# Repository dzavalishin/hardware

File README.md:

# hardware
Misc smart house hardware, kicad designs.

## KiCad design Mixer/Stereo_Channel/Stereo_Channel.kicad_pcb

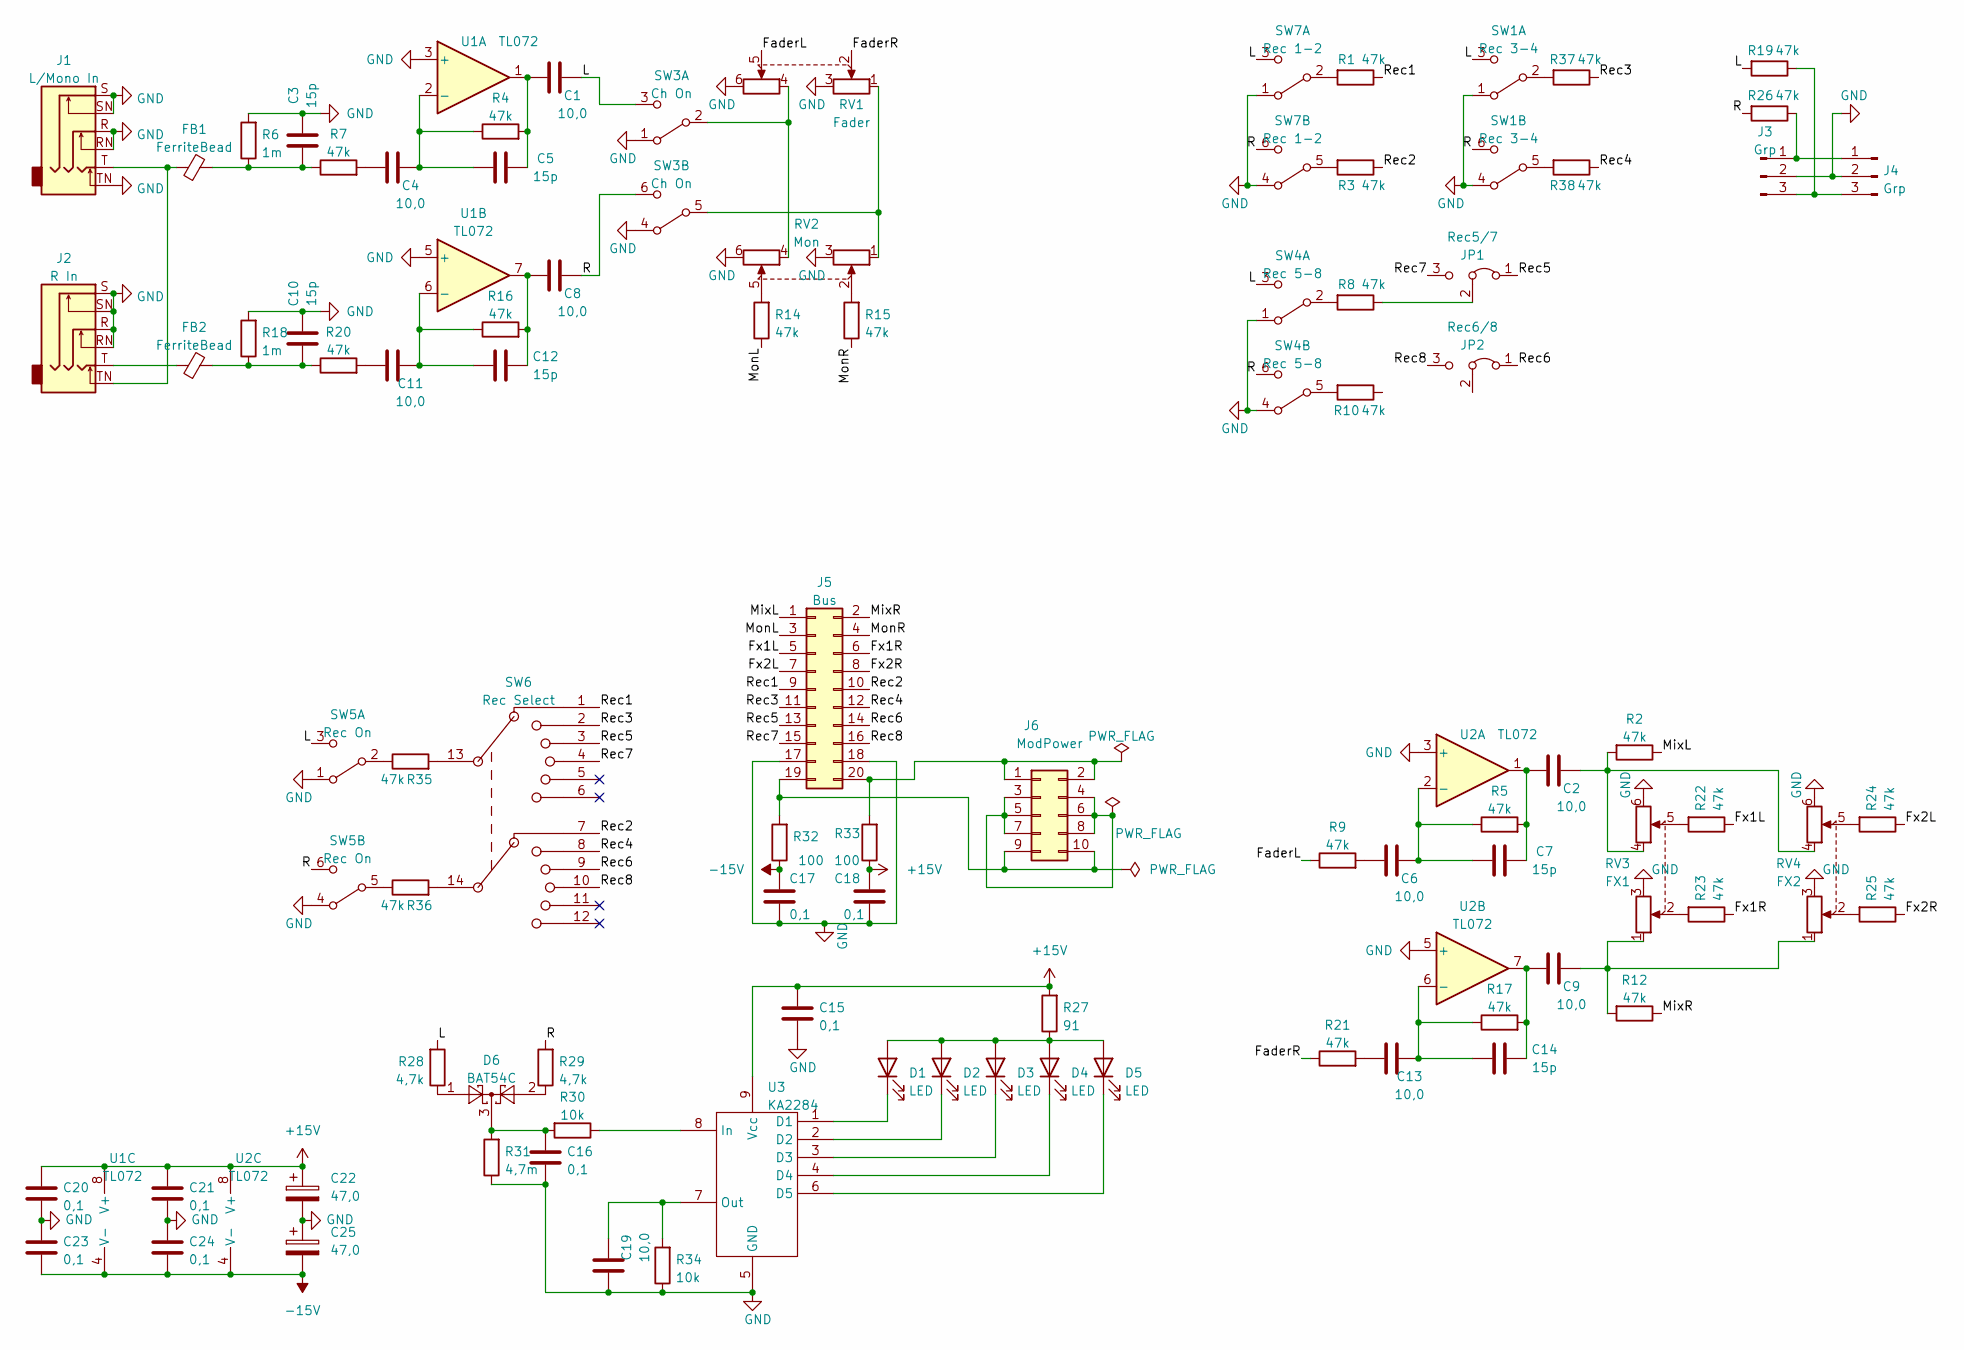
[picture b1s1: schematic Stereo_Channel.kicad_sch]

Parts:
C1, C2, C8, C9: 10,0; C_1206_3216Metric_Pad1.33x1.80mm_HandSolder
C3, C5, C7, C10, C12, C14: 15p; C_0805_2012Metric_Pad1.18x1.45mm_HandSolder
C4, C6, C11, C13, C19: 10,0; C_0805_2012Metric_Pad1.18x1.45mm_HandSolder
C15, C16, C17, C18, C20, C21, C23, C24: 0,1; C_1206_3216Metric_Pad1.33x1.80mm_HandSolder
C22, C25: 47,0; C_0805_2012Metric_Pad1.18x1.45mm_HandSolder
D1, D2, D3, D4, D5: LED; LED_Rectangular_W5.0mm_H2.0mm
D6: BAT54C; SOT-23
FB1, FB2: FerriteBead; L_Axial_L6.6mm_D2.7mm_P10.16mm_Horizontal_Vishay_IM-2
J1: L/Mono In; Jack_6.35mm_Neutrik_NMJ6HCD2_Horizontal
J2: R In; Jack_6.35mm_Neutrik_NMJ6HCD2_Horizontal
J3, J4: Grp; PinHeader_1x03_P2.54mm_Vertical
J5: Bus; PinHeader_2x10_P2.54mm_Vertical
J6: ModPower; PinHeader_2x05_P2.54mm_Vertical
JP1: Rec5/7; SolderJumper-3_P1.3mm_Bridged12_RoundedPad1.0x1.5mm_NumberL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
JP2: Rec6/8; SolderJumper-3_P1.3mm_Bridged12_RoundedPad1.0x1.5mm_NumberL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
R1, R2, R3, R4, R5, R7, R8, R9, R10, R12, R14, R15, R16, R17, R19, R20, R21, R22, R23, R24, R25, R26, R35, R36, R37, R38: 47k; R_1206_3216Metric_Pad1.30x1.75mm_HandSolder
R6, R18: 1m; R_1206_3216Metric_Pad1.30x1.75mm_HandSolder
R27: 91; R_1206_3216Metric_Pad1.30x1.75mm_HandSolder
R28, R29: 4,7k; R_1206_3216Metric_Pad1.30x1.75mm_HandSolder
R30, R34: 10k; R_1206_3216Metric_Pad1.30x1.75mm_HandSolder
R31: 4,7m; R_1206_3216Metric_Pad1.30x1.75mm_HandSolder
R32, R33: 100; R_1206_3216Metric_Pad1.30x1.75mm_HandSolder
RV1: Fader; Slider Pot 60mm
RV2: Mon; RK12 Duplex
RV3: FX1; RK12 Duplex
RV4: FX2; RK12 Duplex
SW1: Rec 3-4; Switch 2P2T 5.5x4.5mm Latched
SW3: Ch On; Switch 2P2T 5.5x4.5mm Latched
SW4: Rec 5-8; Switch 2P2T 5.5x4.5mm Latched
SW5: Rec On; Switch 2P2T 5.5x4.5mm Latched
SW6: Rec Select; SR16 Rotary Switch
SW7: Rec 1-2; Switch 2P2T 5.5x4.5mm Latched
U1, U2: TL072; DIP-8_W7.62mm_LongPads
U3: KA2284; SIP-9_22.3x3mm_P2.54mm

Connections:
+15V: C15.2, C18.2, C20.2, C21.2, C22.1, R27.2, R33.1, U1.8 (V+), U2.8 (V+), U3.9 (Vcc)
-15V: C17.2, C23.1, C24.1, C25.2, R32.1, U1.4 (V-), U2.4 (V-)
/FaderL: R9.1, RV1.5
/FaderR: R21.1, RV1.2
/Fx1L: J5.5, R22.1
/Fx1R: J5.6, R23.1
/Fx2L: J5.7, R24.1
/Fx2R: J5.8, R25.1
/L: C1.2, R19.2, R28.2, SW1.3 (C), SW3.3 (C), SW4.3 (C), SW5.3 (C), SW7.3 (C)
/MixL: J5.1, R2.1
/MixR: J5.2, R12.1
/MonL: J5.3, R14.1
/MonR: J5.4, R15.1
/R: C8.2, R26.2, R29.2, SW1.6 (C), SW3.6 (C), SW4.6 (C), SW5.6 (C), SW7.6 (C)
/Rec1: J5.9, R1.1, SW6.1
/Rec2: J5.10, R3.1, SW6.7
/Rec3: J5.11, R37.1, SW6.2
/Rec4: J5.12, R38.1, SW6.8
/Rec5: J5.13, JP1.1 (A), SW6.3
/Rec6: J5.14, JP2.1 (A), SW6.9
/Rec7: J5.15, JP1.3 (B), SW6.4
/Rec8: J5.16, JP2.3 (B), SW6.10
GND: C3.2, C10.2, C15.1, C16.1, C17.1, C18.1, C19.1, C20.1, C21.1, C22.2, C23.2, C24.2, C25.1, J1.R, J1.RN, J1.S, J1.SN, J1.TN, J2.R, J2.RN, J2.S, J2.SN, J3.2, J4.2, J5.17, J5.18, R6.2, R18.2, R31.1, R34.1, RV1.3, RV1.6, RV2.3, RV2.6, RV3.3, RV3.6, RV4.3, RV4.6, SW1.1 (A), SW1.4 (A), SW3.1 (A), SW3.4 (A), SW4.1 (A), SW4.4 (A), SW5.1 (A), SW5.4 (A), SW7.1 (A), SW7.4 (A), U1.3 (+), U1.5 (+), U2.3 (+), U2.5 (+), U3.5 (GND)
unnamed: C1.1, C5.2, R4.2, U1.1
unnamed: C2.1, C7.2, R5.2, U2.1
unnamed: C2.2, R2.2, RV3.4, RV4.4
unnamed: C3.1, FB1.2, R6.1, R7.1
unnamed: C4.1, R7.2
unnamed: C4.2, C5.1, R4.1, U1.2 (-)
unnamed: C6.1, R9.2
unnamed: C6.2, C7.1, R5.1, U2.2 (-)
unnamed: C9.2, R12.2, RV3.1, RV4.1
unnamed: C10.1, FB2.2, R18.1, R20.1
unnamed: C11.1, R20.2
unnamed: C11.2, C12.1, R16.1, U1.6 (-)
unnamed: C8.1, C12.2, R16.2, U1.7
unnamed: C13.1, R21.2
unnamed: C13.2, C14.1, R17.1, U2.6 (-)
unnamed: C9.1, C14.2, R17.2, U2.7
unnamed: C16.2, D6.3, R30.2, R31.2
unnamed: C19.2, R34.2, U3.7 (Out)
unnamed: D1.1 (K), U3.1 (D1)
unnamed: D1.2 (A), D2.2 (A), D3.2 (A), D4.2 (A), D5.2 (A), R27.1
unnamed: D2.1 (K), U3.2 (D2)
unnamed: D3.1 (K), U3.3 (D3)
unnamed: D4.1 (K), U3.4 (D4)
unnamed: D5.1 (K), U3.6 (D5)
unnamed: D6.1, R28.1
unnamed: D6.2, R29.1
unnamed: FB1.1, J1.T, J2.TN
unnamed: FB2.1, J2.T
unnamed: J3.1, J4.1, R26.1
unnamed: J3.3, J4.3, R19.1
unnamed: J5.19, J6.9, J6.10, R32.2
unnamed: J5.20, J6.1, J6.2, R33.2
unnamed: J6.3, J6.4, J6.5, J6.6, J6.7, J6.8
unnamed: JP1.2 (C), R8.1
unnamed: R1.2, SW7.2 (B)
unnamed: R3.2, SW7.5 (B)
unnamed: R8.2, SW4.2 (B)
unnamed: R10.2, SW4.5 (B)
unnamed: R14.2, RV2.5
unnamed: R15.2, RV2.2
unnamed: R22.2, RV3.5
unnamed: R23.2, RV3.2
unnamed: R24.2, RV4.5
unnamed: R25.2, RV4.2
unnamed: R30.1, U3.8 (In)
unnamed: R37.2, SW1.2 (B)
unnamed: R38.2, SW1.5 (B)
unnamed: RV1.1, RV2.1, SW3.5 (B)
unnamed: RV1.4, RV2.4, SW3.2 (B)
unnamed: R35.1, SW5.2 (B)
unnamed: R36.1, SW5.5 (B)
unnamed: R35.2, SW6.13
unnamed: R36.2, SW6.14

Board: 2 copper layers, 90 parts (66 on the bottom side), 76 nets, no tracks yet.

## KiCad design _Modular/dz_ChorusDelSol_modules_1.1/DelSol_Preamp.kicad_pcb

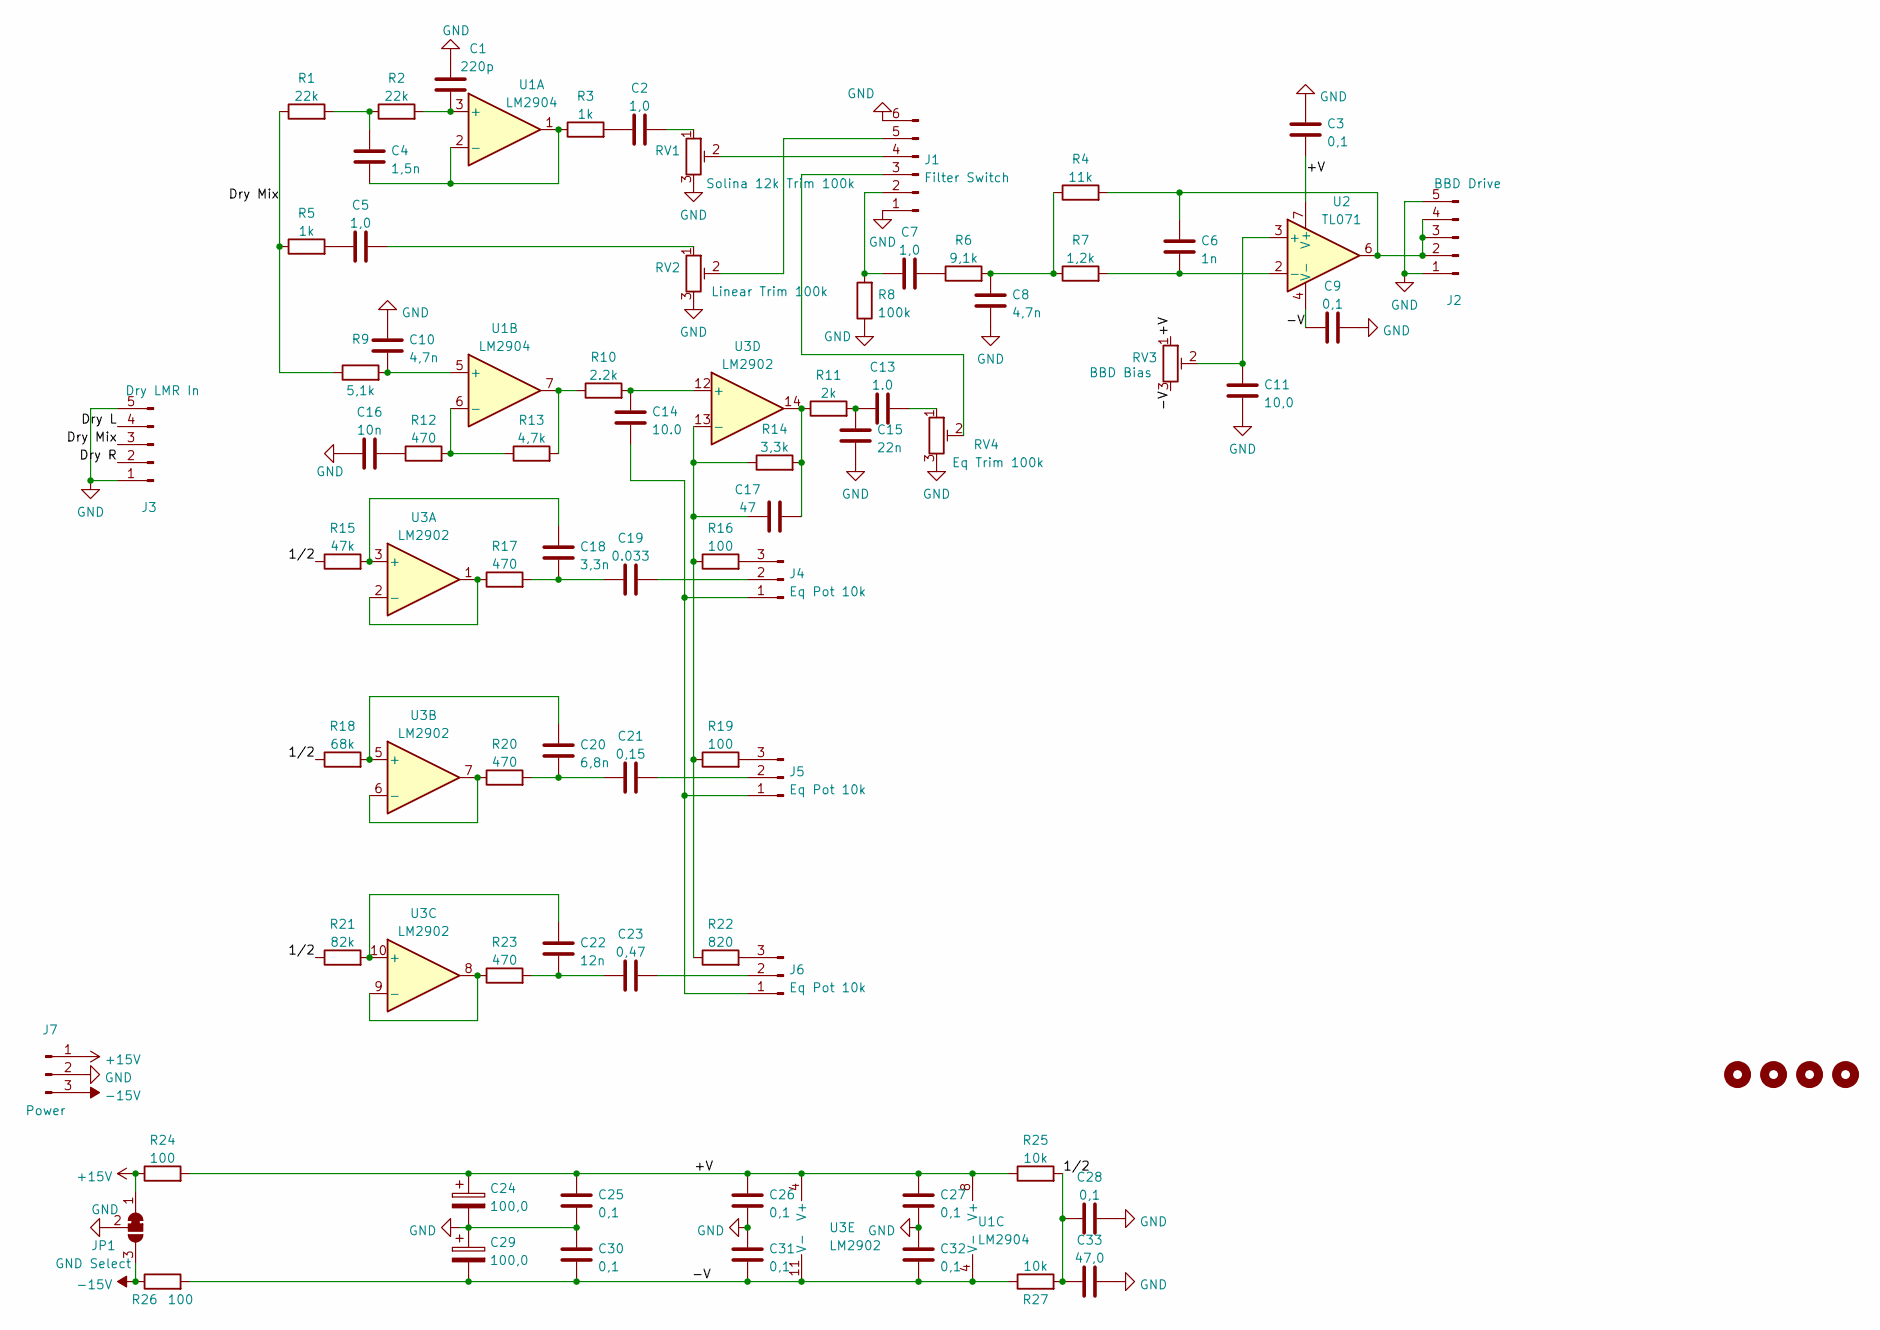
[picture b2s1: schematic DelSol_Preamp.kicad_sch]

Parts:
C1: 220p; C_Disc_D5.0mm_W2.5mm_P2.50mm
C2, C5, C7: 1,0; C_0805_2012Metric_Pad1.18x1.45mm_HandSolder
C3, C9, C25, C26, C27, C28, C30, C31, C32: 0,1; C_1206_3216Metric_Pad1.33x1.80mm_HandSolder
C4: 1,5n; C_Disc_D5.0mm_W2.5mm_P2.50mm
C6: 1n; C_0805_2012Metric_Pad1.18x1.45mm_HandSolder
C8, C10: 4,7n; C_0805_2012Metric_Pad1.18x1.45mm_HandSolder
C11: 10,0; C_0805_2012Metric_Pad1.18x1.45mm_HandSolder
C13: 1.0; C_0805_2012Metric_Pad1.18x1.45mm_HandSolder
C14: 10.0; C_0805_2012Metric_Pad1.18x1.45mm_HandSolder
C15: 22n; C_0805_2012Metric_Pad1.18x1.45mm_HandSolder
C16: 10n; C_0805_2012Metric_Pad1.18x1.45mm_HandSolder
C17: 47; C_0805_2012Metric_Pad1.18x1.45mm_HandSolder
C18: 3,3n; C_0805_2012Metric_Pad1.18x1.45mm_HandSolder
C19: 0.033; C_0805_2012Metric_Pad1.18x1.45mm_HandSolder
C20: 6,8n; C_0805_2012Metric_Pad1.18x1.45mm_HandSolder
C21: 0,15; C_0805_2012Metric_Pad1.18x1.45mm_HandSolder
C22: 12n; C_0805_2012Metric_Pad1.18x1.45mm_HandSolder
C23: 0,47; C_0805_2012Metric_Pad1.18x1.45mm_HandSolder
C24, C29: 100,0; C_Elec_6.3x5.8
C33: 47,0; C_Elec_6.3x5.8
H1, H2, H3, H4: MountingHole; MountingHole_3.2mm_M3
J1: Filter Switch; PinHeader_1x06_P2.54mm_Vertical
J2: BBD Drive; JST_XH_B5B-XH-AM_1x05_P2.50mm_Vertical
J3: Dry LMR In; JST_XH_B5B-XH-AM_1x05_P2.50mm_Vertical
J4, J5, J6: Eq Pot 10k; Potentiometer_Alps_RK097_Single_Horizontal
J7: Power; PinHeader_1x03_P2.54mm_Vertical
JP1: GND Select; PinHeader_1x03_P2.54mm_Vertical
R1, R2: 22k; R_1206_3216Metric_Pad1.30x1.75mm_HandSolder
R3, R5: 1k; R_1206_3216Metric_Pad1.30x1.75mm_HandSolder
R4: 11k; R_1206_3216Metric_Pad1.30x1.75mm_HandSolder
R6: 9,1k; R_1206_3216Metric_Pad1.30x1.75mm_HandSolder
R7: 1,2k; R_1206_3216Metric_Pad1.30x1.75mm_HandSolder
R8: 100k; R_1206_3216Metric_Pad1.30x1.75mm_HandSolder
R9: 5,1k; R_1206_3216Metric_Pad1.30x1.75mm_HandSolder
R10: 2.2k; R_1206_3216Metric_Pad1.30x1.75mm_HandSolder
R11: 2k; R_1206_3216Metric_Pad1.30x1.75mm_HandSolder
R12, R17, R20, R23: 470; R_1206_3216Metric_Pad1.30x1.75mm_HandSolder
R13: 4,7k; R_1206_3216Metric_Pad1.30x1.75mm_HandSolder
R14: 3,3k; R_1206_3216Metric_Pad1.30x1.75mm_HandSolder
R15: 47k; R_1206_3216Metric_Pad1.30x1.75mm_HandSolder
R16, R19, R24, R26: 100; R_1206_3216Metric_Pad1.30x1.75mm_HandSolder
R18: 68k; R_1206_3216Metric_Pad1.30x1.75mm_HandSolder
R21: 82k; R_1206_3216Metric_Pad1.30x1.75mm_HandSolder
R22: 820; R_1206_3216Metric_Pad1.30x1.75mm_HandSolder
R25, R27: 10k; R_1206_3216Metric_Pad1.30x1.75mm_HandSolder
RV1: Solina 12k Trim 100k; Potentiometer_Runtron_RM-065_Vertical
RV2: Linear Trim 100k; Potentiometer_Runtron_RM-065_Vertical
RV3: BBD Bias; Potentiometer_Bourns_3296W_Vertical
RV4: Eq Trim 100k; Potentiometer_Runtron_RM-065_Vertical
U1: LM2904; DIP-8_W7.62mm
U2: TL071; DIP-8_W7.62mm
U3: LM2902; DIP-14_W7.62mm

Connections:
+15V: J7.1, JP1.1 (A), R24.1
-15V: J7.3, JP1.3 (B), R26.1
/1/2: C28.1, C33.1, R15.1, R18.1, R21.1, R25.2, R27.2
/+V: C3.2, C24.1, C25.1, C26.1, C27.1, R24.2, R25.1, RV3.1, U1.8 (V+), U2.7 (V+), U3.4 (V+)
/-V: C9.1, C29.2, C30.2, C31.2, C32.2, R26.2, R27.1, RV3.3, U1.4 (V-), U2.4 (V-), U3.11 (V-)
/Dry L: J3.4
/Dry Mix: J3.3, R1.1, R5.1, R9.1
/Dry R: J3.2
GND: C1.2, C3.1, C8.2, C9.2, C10.1, C11.2, C15.2, C16.1, C24.2, C25.2, C26.2, C27.2, C28.2, C29.1, C30.1, C31.1, C32.1, C33.2, J1.1, J1.6, J2.1, J2.5, J3.1, J3.5, J7.2, JP1.2 (C), R8.1, RV1.3, RV2.3, RV4.3
unnamed: C1.1, R2.2, U1.3 (+)
unnamed: C2.1, R3.2
unnamed: C2.2, RV1.1
unnamed: C4.1, R1.2, R2.1
unnamed: C4.2, R3.1, U1.1, U1.2 (-)
unnamed: C5.1, R5.2
unnamed: C5.2, RV2.1
unnamed: C6.1, J2.2, J2.3, J2.4, R4.2, U2.6
unnamed: C6.2, R7.2, U2.2 (-)
unnamed: C7.1, J1.2, R8.2
unnamed: C7.2, R6.1
unnamed: C8.1, R4.1, R6.2, R7.1
unnamed: C10.2, R9.2, U1.5 (+)
unnamed: C13.1, RV4.1
unnamed: C13.2, C15.1, R11.2
unnamed: C14.1, J4.1, J5.1, J6.1
unnamed: C14.2, R10.2, U3.12 (+)
unnamed: C16.2, R12.1
unnamed: C17.1, R14.1, R16.1, R19.1, R22.1, U3.13 (-)
unnamed: C17.2, R11.1, R14.2, U3.14
unnamed: C18.1, R15.2, U3.3 (+)
unnamed: C18.2, C19.1, R17.2
unnamed: C19.2, J4.2
unnamed: C20.1, R18.2, U3.5 (+)
unnamed: C20.2, C21.1, R20.2
unnamed: C21.2, J5.2
unnamed: C22.1, R21.2, U3.10 (+)
unnamed: C22.2, C23.1, R23.2
unnamed: C23.2, J6.2
unnamed: J1.3, RV4.2
unnamed: J1.4, RV1.2
unnamed: J1.5, RV2.2
unnamed: J4.3, R16.2
unnamed: J5.3, R19.2
unnamed: J6.3, R22.2
unnamed: R10.1, R13.2, U1.7
unnamed: R12.2, R13.1, U1.6 (-)
unnamed: R17.1, U3.1, U3.2 (-)
unnamed: R20.1, U3.6 (-), U3.7
unnamed: R23.1, U3.8, U3.9 (-)
unnamed: C11.1, RV3.2, U2.3 (+)

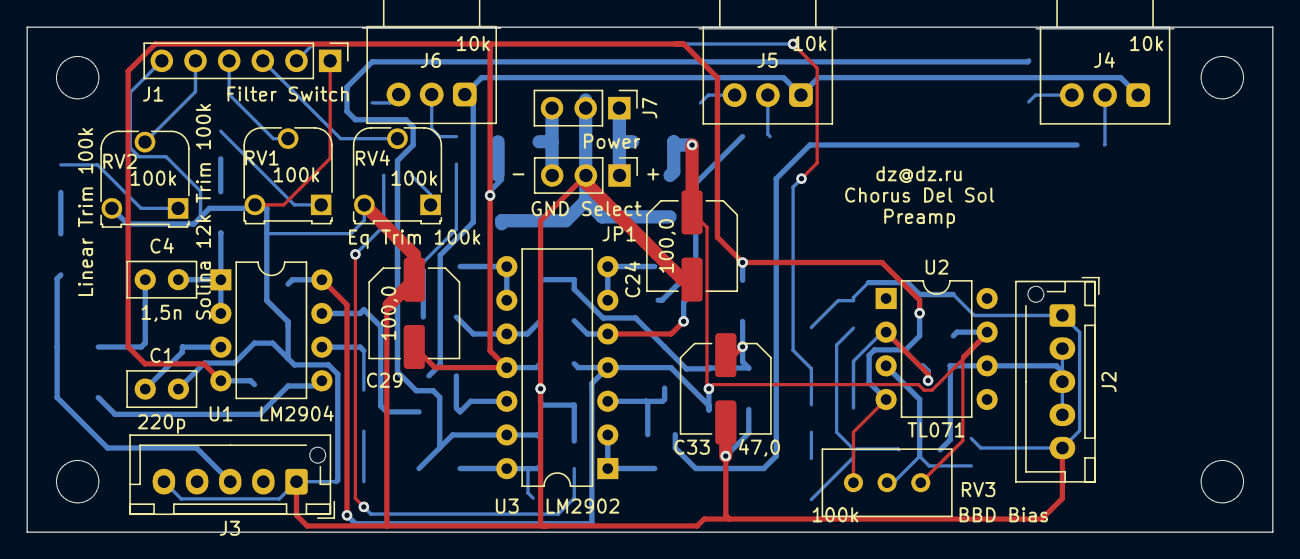
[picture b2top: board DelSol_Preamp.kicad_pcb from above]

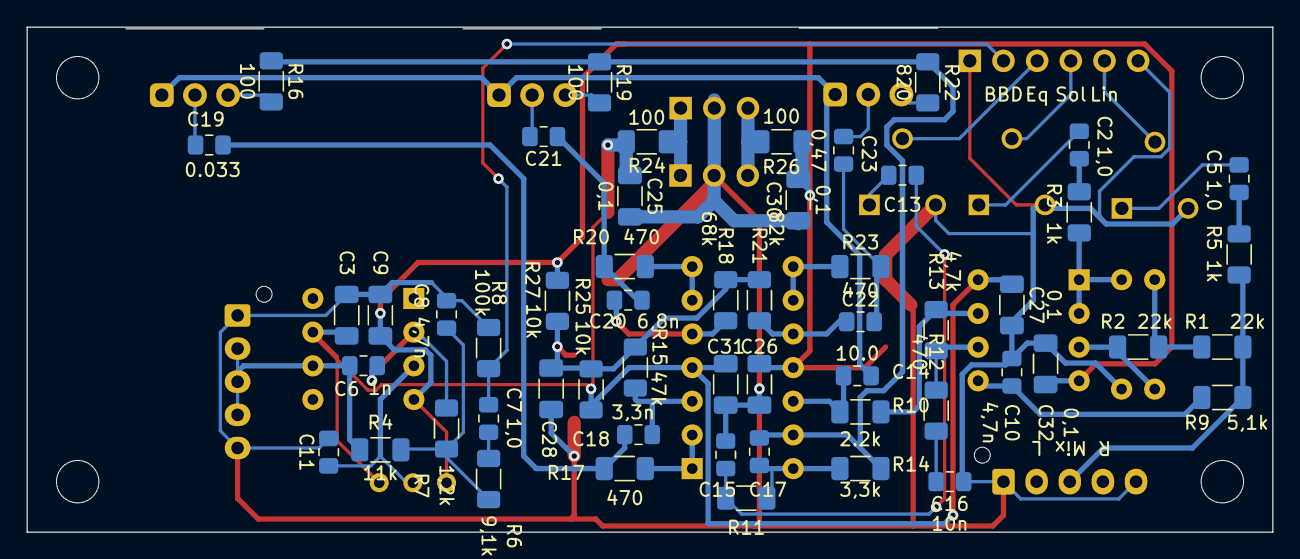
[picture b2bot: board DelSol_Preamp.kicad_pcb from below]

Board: 2 copper layers, 94.0 x 38.1 mm, 78 parts (54 on the bottom side), 48 nets.

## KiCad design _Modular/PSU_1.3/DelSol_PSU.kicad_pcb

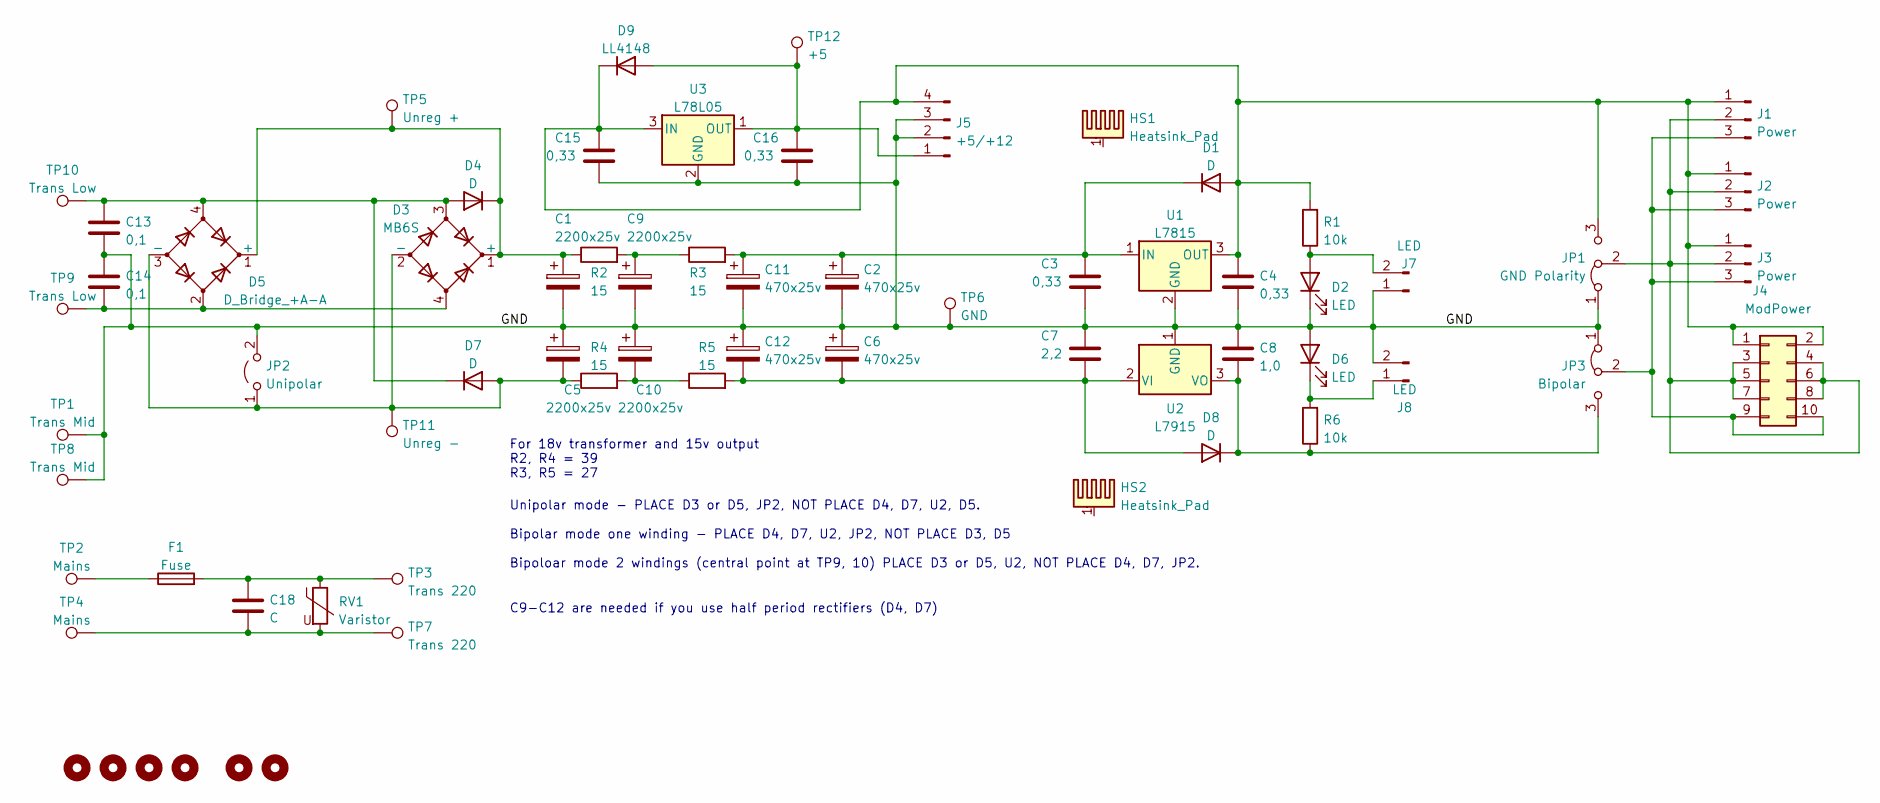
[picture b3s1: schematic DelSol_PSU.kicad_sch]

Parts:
C1, C5, C9, C10: 2200x25v; CP_Radial_D13.0mm_P5.00mm
C2, C6, C11, C12: 470x25v; CP_Radial_D13.0mm_P5.00mm
C3, C4, C15, C16: 0,33; C_0805_2012Metric_Pad1.18x1.45mm_HandSolder
C7: 2,2; C_0805_2012Metric_Pad1.18x1.45mm_HandSolder
C8: 1,0; C_0805_2012Metric_Pad1.18x1.45mm_HandSolder
C13, C14: 0,1; C_Rect_L13.0mm_W6.0mm_P10.00mm_FKS3_FKP3_MKS4
C18: C; C_Rect_L13.0mm_W6.0mm_P10.00mm_FKS3_FKP3_MKS4
D1, D4, D7, D8: D; D_SMA-SMB_Universal_Handsoldering
D2, D6: LED; LED_1206_3216Metric_Pad1.42x1.75mm_HandSolder
D3: MB6S; TO-269AA
D5: D_Bridge_+A-A; Diode_Bridge_Round_D9.0mm
D9: LL4148; D_MiniMELF
F1: Fuse; Fuseholder_Clip-5x20mm_Keystone_3512_Inline_P23.62x7.27mm_D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
H1, H2, H3, H4, H5, H6: MountingHole; MountingHole_3.2mm_M3
HS1, HS2: Heatsink_Pad; Heatsink_TO_220
J1, J2, J3: Power; PinHeader_1x03_P2.54mm_Vertical
J4: ModPower; PinHeader_2x05_P2.54mm_Vertical
J5: +5/+12; Molex_KK-254_AE-6410-04A_1x04_P2.54mm_Vertical
J7, J8: LED; PinHeader_1x02_P2.54mm_Vertical
JP1: GND Polarity; PinHeader_1x03_P2.54mm_Vertical
JP2: Unipolar; TestPoint_2Pads_Pitch2.54mm_Drill0.8mm
JP3: Bipolar; PinHeader_1x03_P2.54mm_Vertical
R1, R6: 10k; R_1206_3216Metric_Pad1.30x1.75mm_HandSolder
R2, R3, R4, R5: 15; R_Axial_DIN0516_L15.5mm_D5.0mm_P5.08mm_Vertical
RV1: Varistor; RV_Disc_D15.5mm_W3.9mm_P7.5mm
TP1, TP8: Trans Mid; TestPoint_THTPad_3.0x3.0mm_Drill1.5mm
TP2, TP4: Mains; TestPoint_THTPad_2.0x2.0mm_Drill1.0mm
TP3, TP7: Trans 220; TestPoint_THTPad_3.0x3.0mm_Drill1.5mm
TP5: Unreg +; TestPoint_THTPad_3.0x3.0mm_Drill1.5mm
TP6: GND; TestPoint_THTPad_3.0x3.0mm_Drill1.5mm
TP9, TP10: Trans Low; TestPoint_THTPad_3.0x3.0mm_Drill1.5mm
TP11: Unreg -; TestPoint_THTPad_3.0x3.0mm_Drill1.5mm
TP12: +5; TestPoint_THTPad_3.0x3.0mm_Drill1.5mm
U1: L7815; TO-220-3_Vertical
U2: L7915; TO-220-3_Vertical
U3: L78L05; SOT-89-3

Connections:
/GND: C1.2, C2.2, C3.2, C4.2, C5.1, C6.1, C7.1, C8.1, C9.2, C10.1, C11.2, C12.1, C13.2, C14.1, C15.2, C16.2, D2.1 (K), D6.2 (A), J5.2, J5.3, J7.1, J8.2, JP1.1 (A), JP2.2 (B), JP3.1 (A), TP1.1, TP6.1, TP8.1, U1.2 (GND), U2.1 (GND), U3.2 (GND)
unnamed: C4.1, C15.1, D1.2 (A), D9.1 (K), J1.1, J2.1, J3.1, J4.1, J4.2, J5.4, JP1.3 (B), R1.2, U1.3 (OUT), U3.3 (IN)
unnamed: C5.2, D3.2 (-), D5.3 (-), D7.2 (A), JP2.1 (A), R4.1, TP11.1
unnamed: C8.2, D8.1 (K), JP3.3 (B), R6.1, U2.3 (VO)
unnamed: C9.1, R2.2, R3.1
unnamed: C10.2, R4.2, R5.1
unnamed: C2.1, C3.1, C11.1, D1.1 (K), R3.2, U1.1 (IN)
unnamed: C6.2, C7.2, C12.2, D8.2 (A), R5.2, U2.2 (VI)
unnamed: C13.1, D3.3, D4.2 (A), D5.4, D7.1 (K), TP10.1
unnamed: C14.2, D3.4, D5.2, TP9.1
unnamed: C18.1, F1.2, RV1.1, TP3.1
unnamed: C18.2, RV1.2, TP4.1, TP7.1
unnamed: D2.2 (A), J7.2, R1.1
unnamed: C1.1, D3.1 (+), D4.1 (K), D5.1 (+), R2.1, TP5.1
unnamed: D6.1 (K), J8.1, R6.2
unnamed: F1.1, TP2.1
unnamed: J1.2, J2.2, J3.2, J4.3, J4.4, J4.5, J4.6, J4.7, J4.8, JP1.2 (C)
unnamed: J1.3, J2.3, J3.3, J4.9, J4.10, JP3.2 (C)
unnamed: C16.1, D9.2 (A), J5.1, TP12.1, U3.1 (OUT)

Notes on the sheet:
Unipolar mode - PLACE D3 or D5, JP2, NOT PLACE D4, D7, U2, D5. Bipolar mode one winding - PLACE D4, D7, U2, JP2, NOT PLACE D3, D5 Bipoloar mode 2 windings (central point at TP9, 10) PLACE D3 or D5, U2, NOT PLACE D4, D7, JP2.
C9-C12 are needed if you use half period rectifiers (D4, D7)
For 18v transformer and 15v output R2, R4 = 39 R3, R5 = 27

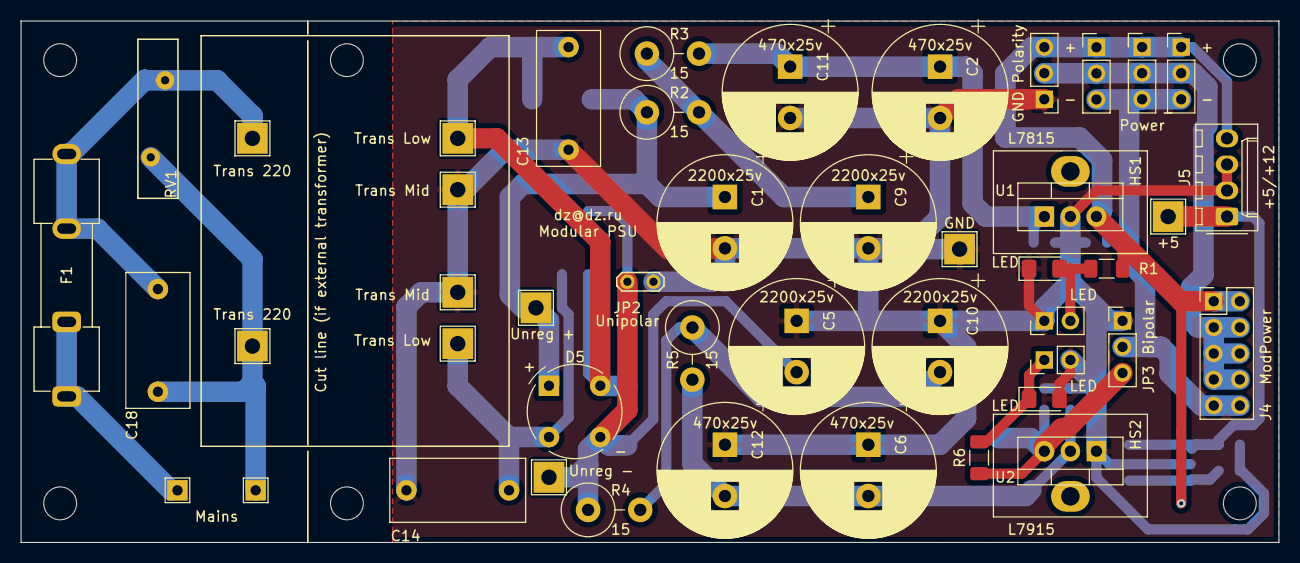
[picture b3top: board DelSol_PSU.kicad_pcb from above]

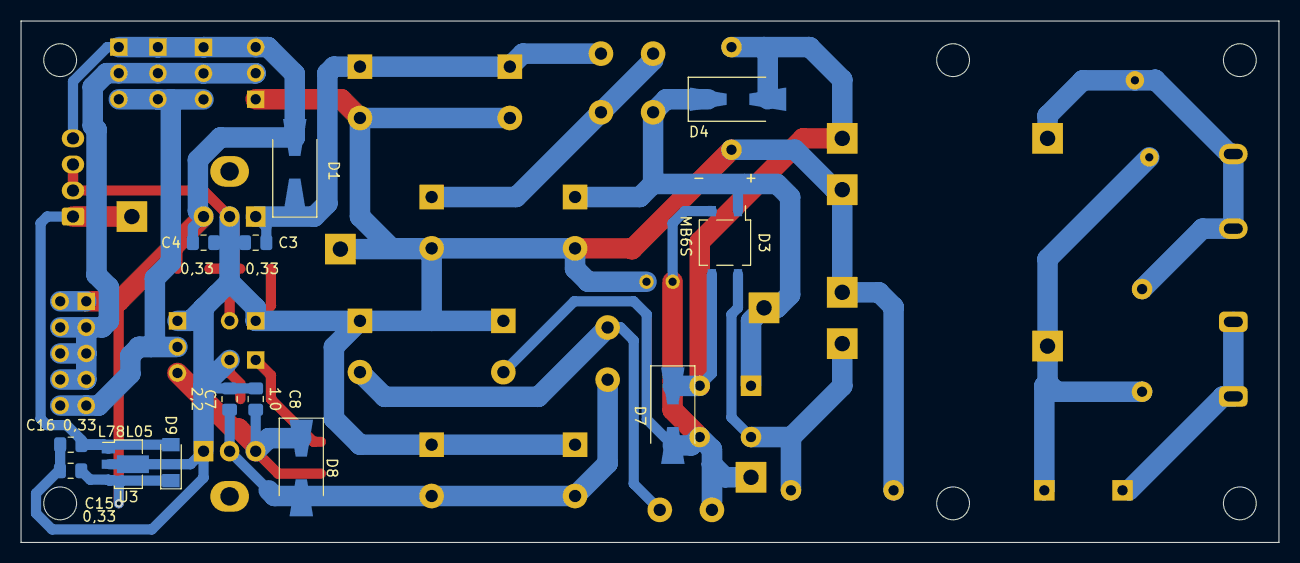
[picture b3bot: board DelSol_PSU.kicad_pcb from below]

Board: 2 copper layers, 122.6 x 50.8 mm, 67 parts (13 on the bottom side), 19 nets.

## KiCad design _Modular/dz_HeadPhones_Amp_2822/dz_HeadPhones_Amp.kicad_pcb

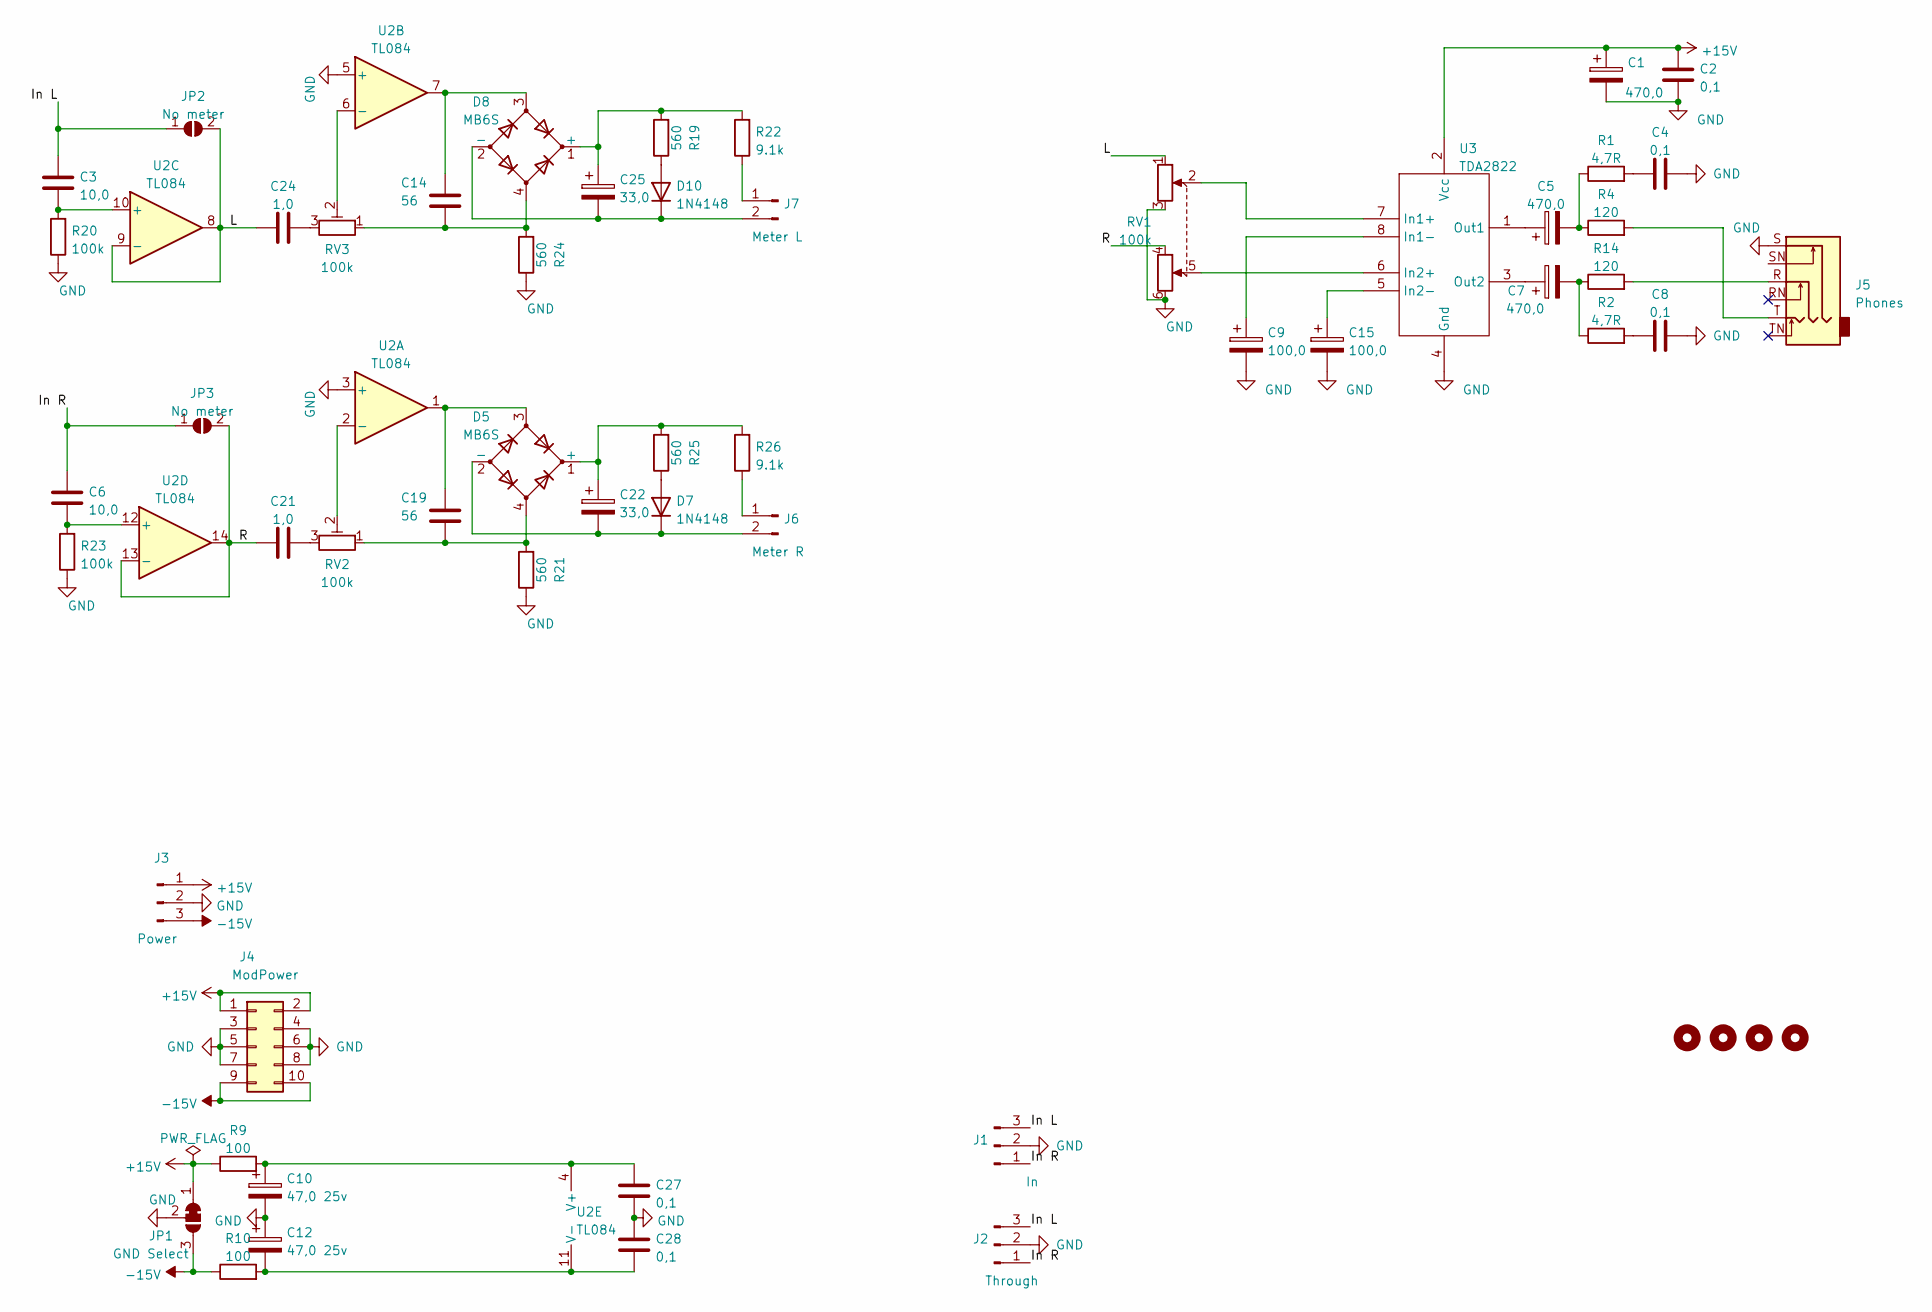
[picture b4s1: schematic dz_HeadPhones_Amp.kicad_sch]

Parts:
C1, C5, C7: 470,0; CP_Radial_D10.0mm_P5.00mm
C2, C4, C8, C27, C28: 0,1; C_1206_3216Metric_Pad1.33x1.80mm_HandSolder
C3, C6: 10,0; C_0805_2012Metric_Pad1.18x1.45mm_HandSolder
C9, C15: 100,0; CP_Radial_D5.0mm_P2.50mm
C10, C12: 47,0 25v; CP_Radial_D5.0mm_P2.50mm
C14, C19: 56; C_Disc_D5.0mm_W2.5mm_P2.50mm
C21, C24: 1,0; C_0805_2012Metric_Pad1.18x1.45mm_HandSolder
C22, C25: 33,0; CP_Radial_D5.0mm_P2.50mm
D5, D8: MB6S; TO-269AA
D7, D10: 1N4148; D_DO-35_SOD27_P2.54mm_Vertical_KathodeUp
H1, H2, H3, H4: MountingHole; MountingHole_3.2mm_M3
J1: In; PinHeader_1x03_P2.54mm_Vertical
J2: Through; PinHeader_1x03_P2.54mm_Vertical
J3: Power; PinHeader_1x03_P2.54mm_Vertical
J4: ModPower; PinHeader_2x05_P2.54mm_Vertical
J5: Phones; Jack_6.35mm_Neutrik_NMJ6HCD2_Horizontal
J6: Meter R; PinHeader_1x02_P2.54mm_Vertical
J7: Meter L; PinHeader_1x02_P2.54mm_Vertical
JP1: GND Select; PinHeader_1x03_P2.54mm_Vertical
JP2, JP3: No meter; PinHeader_1x02_P2.54mm_Vertical
R1, R2: 4,7R; R_Axial_DIN0207_L6.3mm_D2.5mm_P2.54mm_Vertical
R4, R14: 120; R_1206_3216Metric_Pad1.30x1.75mm_HandSolder
R9, R10: 100; R_1206_3216Metric_Pad1.30x1.75mm_HandSolder
R19, R21, R24, R25: 560; R_1206_3216Metric_Pad1.30x1.75mm_HandSolder
R20, R23: 100k; R_1206_3216Metric_Pad1.30x1.75mm_HandSolder
R22, R26: 9.1k; R_1206_3216Metric_Pad1.30x1.75mm_HandSolder
RV1: 100k; Potentiometer_Alps_RK097_Dual_Horizontal
RV2, RV3: 100k; Potentiometer_Runtron_RM-065_Vertical
U2: TL084; DIP-14_W7.62mm_Socket_LongPads
U3: TDA2822; DIP-8_W7.62mm_Socket_LongPads

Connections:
+15V: C1.1, C2.1, J3.1, J4.1, J4.2, JP1.1 (A), R9.1, U3.2 (Vcc)
-15V: J3.3, J4.9, J4.10, JP1.3 (B), R10.1
/In L: C3.1, J1.3, J2.3, JP2.1 (A)
/In R: C6.1, J1.1, J2.1, JP3.1 (A)
/L: C24.1, JP2.2 (B), RV1.1, U2.8, U2.9 (-)
/R: C21.1, JP3.2 (B), RV1.4, U2.13 (-), U2.14
GND: C1.2, C2.2, C4.2, C8.2, C9.2, C10.2, C12.1, C15.2, C27.2, C28.1, J1.2, J2.2, J3.2, J4.3, J4.4, J4.5, J4.6, J4.7, J4.8, J5.S, JP1.2 (C), R20.1, R21.1, R23.1, R24.1, RV1.3, RV1.6, U2.3 (+), U2.5 (+), U3.4 (Gnd)
unnamed: C3.2, R20.2, U2.10 (+)
unnamed: C4.1, R1.2
unnamed: C5.1, U3.1 (Out1)
unnamed: C6.2, R23.2, U2.12 (+)
unnamed: C7.1, U3.3 (Out2)
unnamed: C8.1, R2.2
unnamed: C9.1, U3.8 (In1-)
unnamed: C10.1, C27.1, R9.2, U2.4 (V+)
unnamed: C12.2, C28.2, R10.2, U2.11 (V-)
unnamed: C14.1, D8.3, U2.7
unnamed: C14.2, D8.4, R24.2, RV3.1
unnamed: C15.1, U3.5 (In2-)
unnamed: C19.1, D5.3, U2.1
unnamed: C19.2, D5.4, R21.2, RV2.1
unnamed: C21.2, RV2.3
unnamed: C22.1, D5.1 (+), R25.2, R26.2
unnamed: C22.2, D5.2 (-), D7.1 (K), J6.2
unnamed: C24.2, RV3.3
unnamed: C25.1, D8.1 (+), R19.2, R22.2
unnamed: C25.2, D8.2 (-), D10.1 (K), J7.2
unnamed: D7.2 (A), R25.1
unnamed: D10.2 (A), R19.1
unnamed: J6.1, R26.1
unnamed: J7.1, R22.1
unnamed: C5.2, R1.1, R4.1
unnamed: J5.T, R4.2
unnamed: C7.2, R2.1, R14.1
unnamed: J5.R, R14.2
unnamed: RV1.2, U3.7 (In1+)
unnamed: RV1.5, U3.6 (In2+)
unnamed: RV2.2, U2.2 (-)
unnamed: RV3.2, U2.6 (-)
